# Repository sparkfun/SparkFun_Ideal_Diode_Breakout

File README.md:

SparkFun Ideal Diode Breakout
========================================

[*SparkFun Ideal Diode Breakout (COM-27925)*](https://www.sparkfun.com/products/27925)

Keep your project powered up during power supply hot-swaps with the SparkFun Ideal Diode Breakout. This compact (15.2mm x 12.7mm) breakout board features four channels and ground connections, providing reliable one-way voltage control. Ideal diodes minimize forward voltage drop, internal power dissipation, and reverse DC leakage current, making them perfect for dynamic power selection and switchover, over-voltage protection, and projects requiring stable power input.

This breakout boasts impressive performance with a typical forward voltage drop as low as 8mV at 0.1A (20V input) and 62mV at 1A (20V input), ensuring efficient power delivery. For higher current applications, the forward voltage drop is typically 275mV at 4A (20V input). The typical on-resistance ranges from 69mΩ (20V, 4A) to 260mΩ (1.8V, 0.1A), depending on the input voltage and current. Reverse leakage current is minimal, ranging from -50µA to -560µA depending on reverse voltage and again on the input voltage.

Repository Contents
-------------------

* **/Hardware** - KiCAD design files (.brd, .sch)
* **/Documents** - Files related to the hardware on the board
* **/docs** - Hookup guide files

Documentation
--------------
* **[Hookup Guide](https://docs.sparkfun.com/SparkFun_Ideal_Diode_Breakout)** - Basic hookup guide for the SparkFun Ideal Diode Breakout

License Information
-------------------

This product is _**open source**_! 

Please review the LICENSE.md file for license information. 

If you have any questions or concerns on licensing, please contact technical support on our [SparkFun forums](https://forum.sparkfun.com/viewforum.php?f=152).

Distributed as-is; no warranty is given.

- Your friends at SparkFun.

_<COLLABORATION CREDIT>_

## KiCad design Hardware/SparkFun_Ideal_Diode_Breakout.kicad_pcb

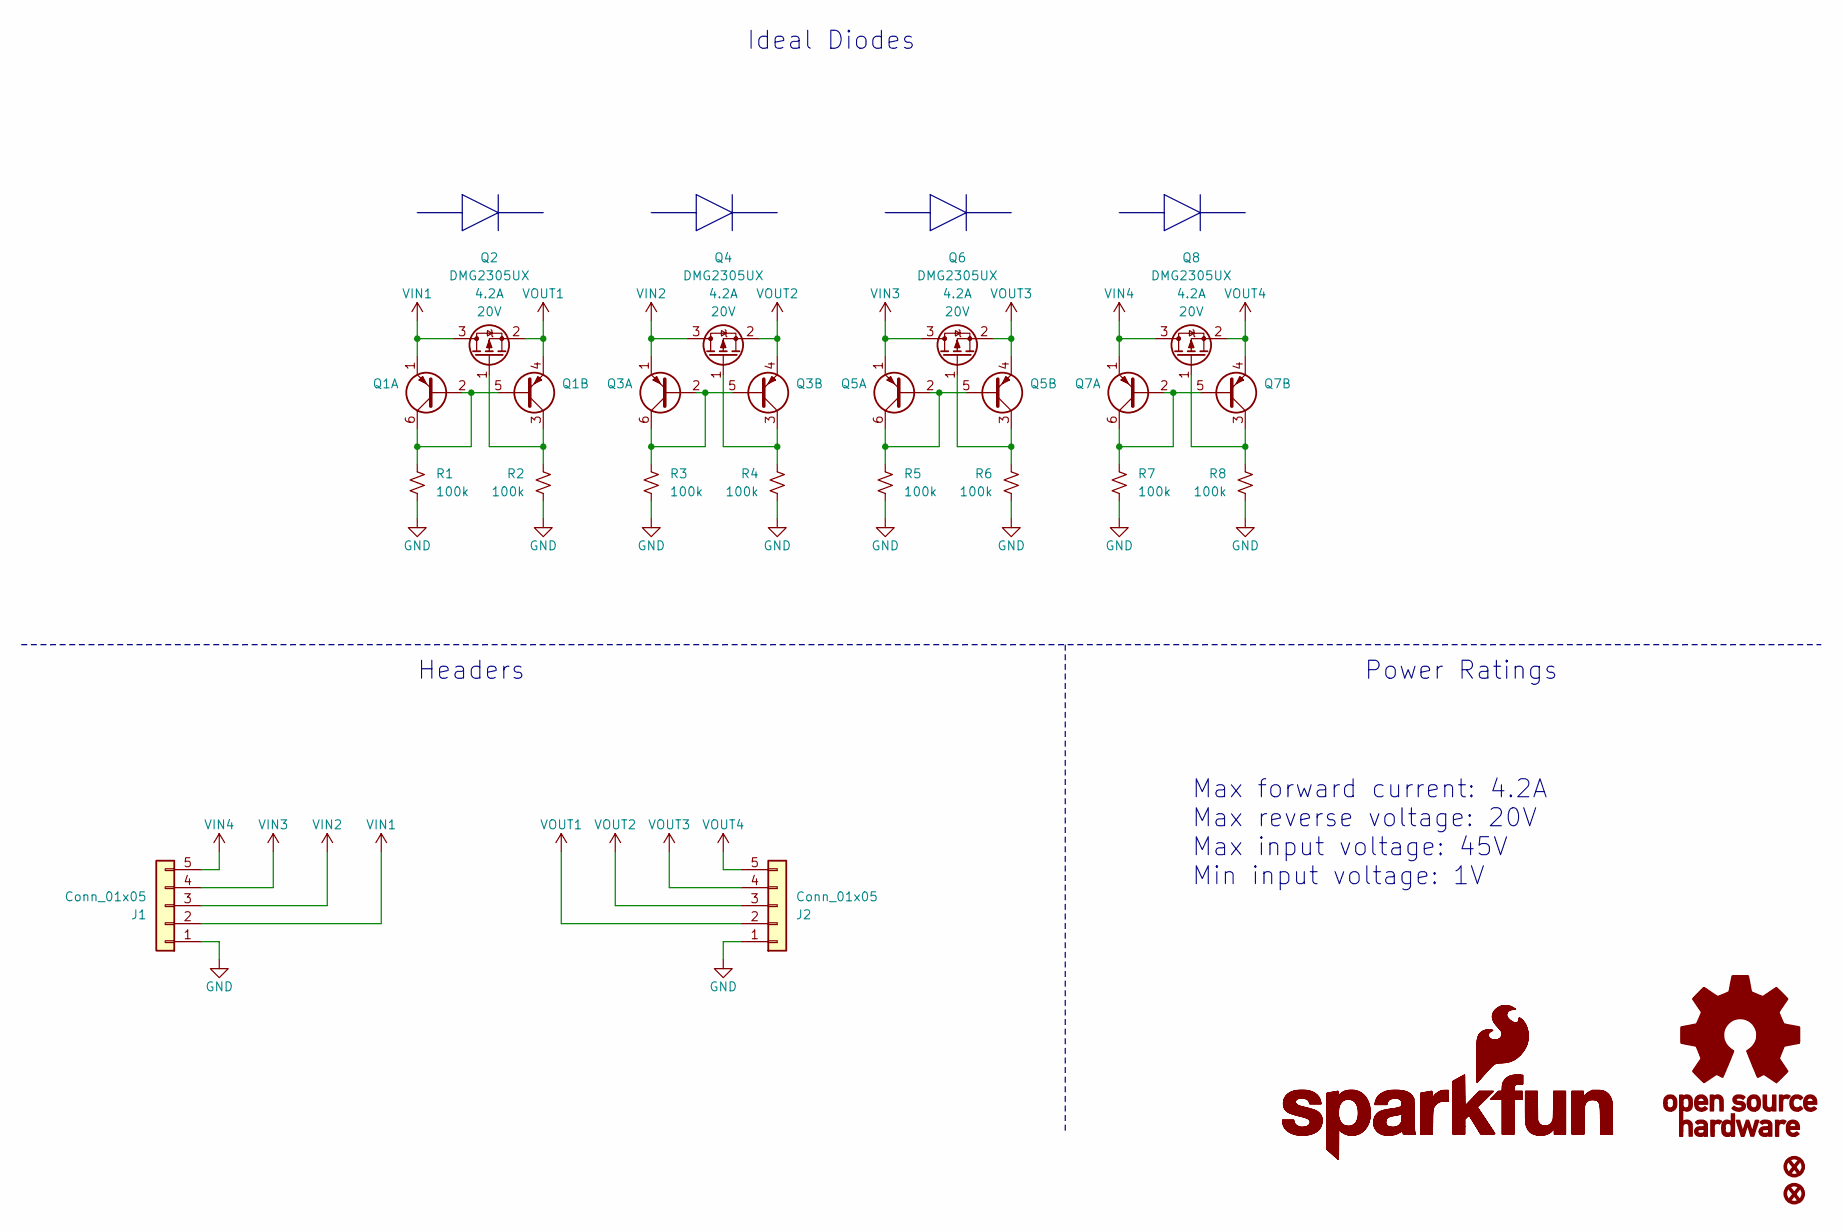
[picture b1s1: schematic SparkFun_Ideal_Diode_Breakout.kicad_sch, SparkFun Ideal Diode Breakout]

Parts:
FID1, FID4: Fiducial_0.5mm; Fiducial_0.5mm_Mask1mm
G1: SparkFun_Logo; SparkFun_Logo_8mm
G2: SparkFun_Logo
G3: OSHW_Logo; Creative_Commons_License
J1, J2: Conn_01x05; 1x05
Q1, Q3, Q5, Q7: BCM857BS-7-F; SOT-323
Q2, Q4, Q6, Q8: DMG2305UX; SOT23-3
R1, R2, R3, R4, R5, R6, R7, R8: 100k; R_0402_1005Metric

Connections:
GND: J1.1, J2.1, R1.1, R2.1, R3.1, R4.1, R5.1, R6.1, R7.1, R8.1
unnamed: Q1.2 (B), Q1.5 (B), Q1.6 (C), R1.2
unnamed: Q1.3 (C), Q2.1 (G), R2.2
unnamed: Q3.2 (B), Q3.5 (B), Q3.6 (C), R3.2
unnamed: Q3.3 (C), Q4.1 (G), R4.2
unnamed: Q5.2 (B), Q5.5 (B), Q5.6 (C), R5.2
unnamed: Q5.3 (C), Q6.1 (G), R6.2
unnamed: Q7.2 (B), Q7.5 (B), Q7.6 (C), R7.2
unnamed: Q7.3 (C), Q8.1 (G), R8.2
VIN1: J1.2, Q1.1 (E), Q2.3 (D)
VIN2: J1.3, Q3.1 (E), Q4.3 (D)
VIN3: J1.4, Q5.1 (E), Q6.3 (D)
VIN4: J1.5, Q7.1 (E), Q8.3 (D)
VOUT1: J2.2, Q1.4 (E), Q2.2 (S)
VOUT2: J2.3, Q3.4 (E), Q4.2 (S)
VOUT3: J2.4, Q5.4 (E), Q6.2 (S)
VOUT4: J2.5, Q7.4 (E), Q8.2 (S)

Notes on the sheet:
Max forward current: 4.2A Max reverse voltage: 20V Max input voltage: 45V Min input voltage: 1V
Headers
Power Ratings
Ideal Diodes

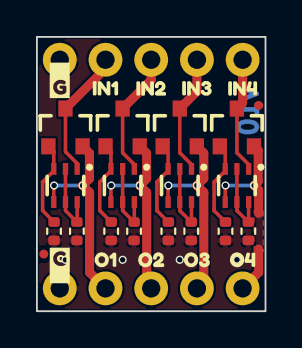
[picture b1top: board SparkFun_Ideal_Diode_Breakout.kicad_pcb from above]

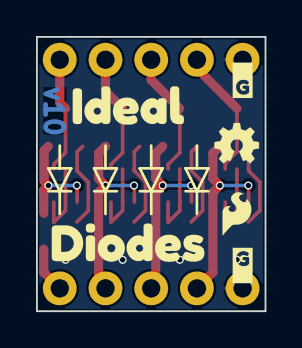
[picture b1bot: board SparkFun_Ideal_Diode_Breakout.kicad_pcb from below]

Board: 2 copper layers, 12.7 x 15.2 mm, 36 parts (5 on the bottom side), 17 nets.

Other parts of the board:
Ref**: Val**; OSHW_Logo_2.5mm
kibuzzard-6765BB94: G***; kibuzzard-6765BB94
kibuzzard-6765BBA3: G***; kibuzzard-6765BBA3
kibuzzard-6765D0F5: G***; kibuzzard-6765D0F5
kibuzzard-6765D0FB: G***; kibuzzard-6765D0FB
kibuzzard-6765D14E: G***; kibuzzard-6765D14E
kibuzzard-6765D15F: G***; kibuzzard-6765D15F
kibuzzard-6765D25C, kibuzzard-6765D25C#2: G***; kibuzzard-6765D25C
kibuzzard-6765D145: G***; kibuzzard-6765D145
kibuzzard-6765D154: G***; kibuzzard-6765D154
kibuzzard-6765D159: G***; kibuzzard-6765D159
kibuzzard-6765D166: G***; kibuzzard-6765D166
kibuzzard-6765D292, kibuzzard-6765D292#2: G***; kibuzzard-6765D292

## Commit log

2024-12-20 Add initial design
2024-12-20 Design review updates
    Update page info on schematic and board
    Separate schematic sections with lines and header text
    Add power ratings
    Add diode symbols to schematic
    Change GND symbol silk to "G"
    Check and exclude ERC and DRC errors
2024-12-20 Change to 2 layer
2025-01-31 Initial Pass of Documentation
    Not complete - just getting the bones in and what I have so far.
2025-02-04 Update ratings and add typical characteristics
2025-02-04 Testing build options and adding diode graphs
2025-02-07 Updating tutorial
    Adding images and hardware updates
2025-02-07 Fixing Links
2025-02-11 Almost final checkin of docs
2025-02-11 Updated description
2025-02-11 Removing Hardware Hookup
    Moving Hardware Hookup to the Quick Start Guide.
2025-02-13 Fixing Header error
2025-02-13 Deployed b248c1b with MkDocs version: 1.6.1
2025-07-08 Fix missing wire in hookup guide circuit
    Fixes #1
2025-07-08 Updating workflows file
    Updating the GH pages workflow file to latest version.
2025-07-08 Deployed 19157b8 with MkDocs version: 1.6.1
2025-07-08 Update quick_start.md
    Updating quick start to add updated image.
2025-07-08 Deployed c50c300 with MkDocs version: 1.6.1
2026-06-03 Deployed c950f43 with MkDocs version: 1.6.1

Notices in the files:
parts and their libraries:
https://creativecommons.org/licenses/by-sa/4.0
Released under the Creative Commons Attribution Share-Alike 4.0 License
